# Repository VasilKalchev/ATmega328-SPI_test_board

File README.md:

# ATmega328-SPI_test_board
ATmega328 test board connected to an SPI device and a few inputs and outputs.

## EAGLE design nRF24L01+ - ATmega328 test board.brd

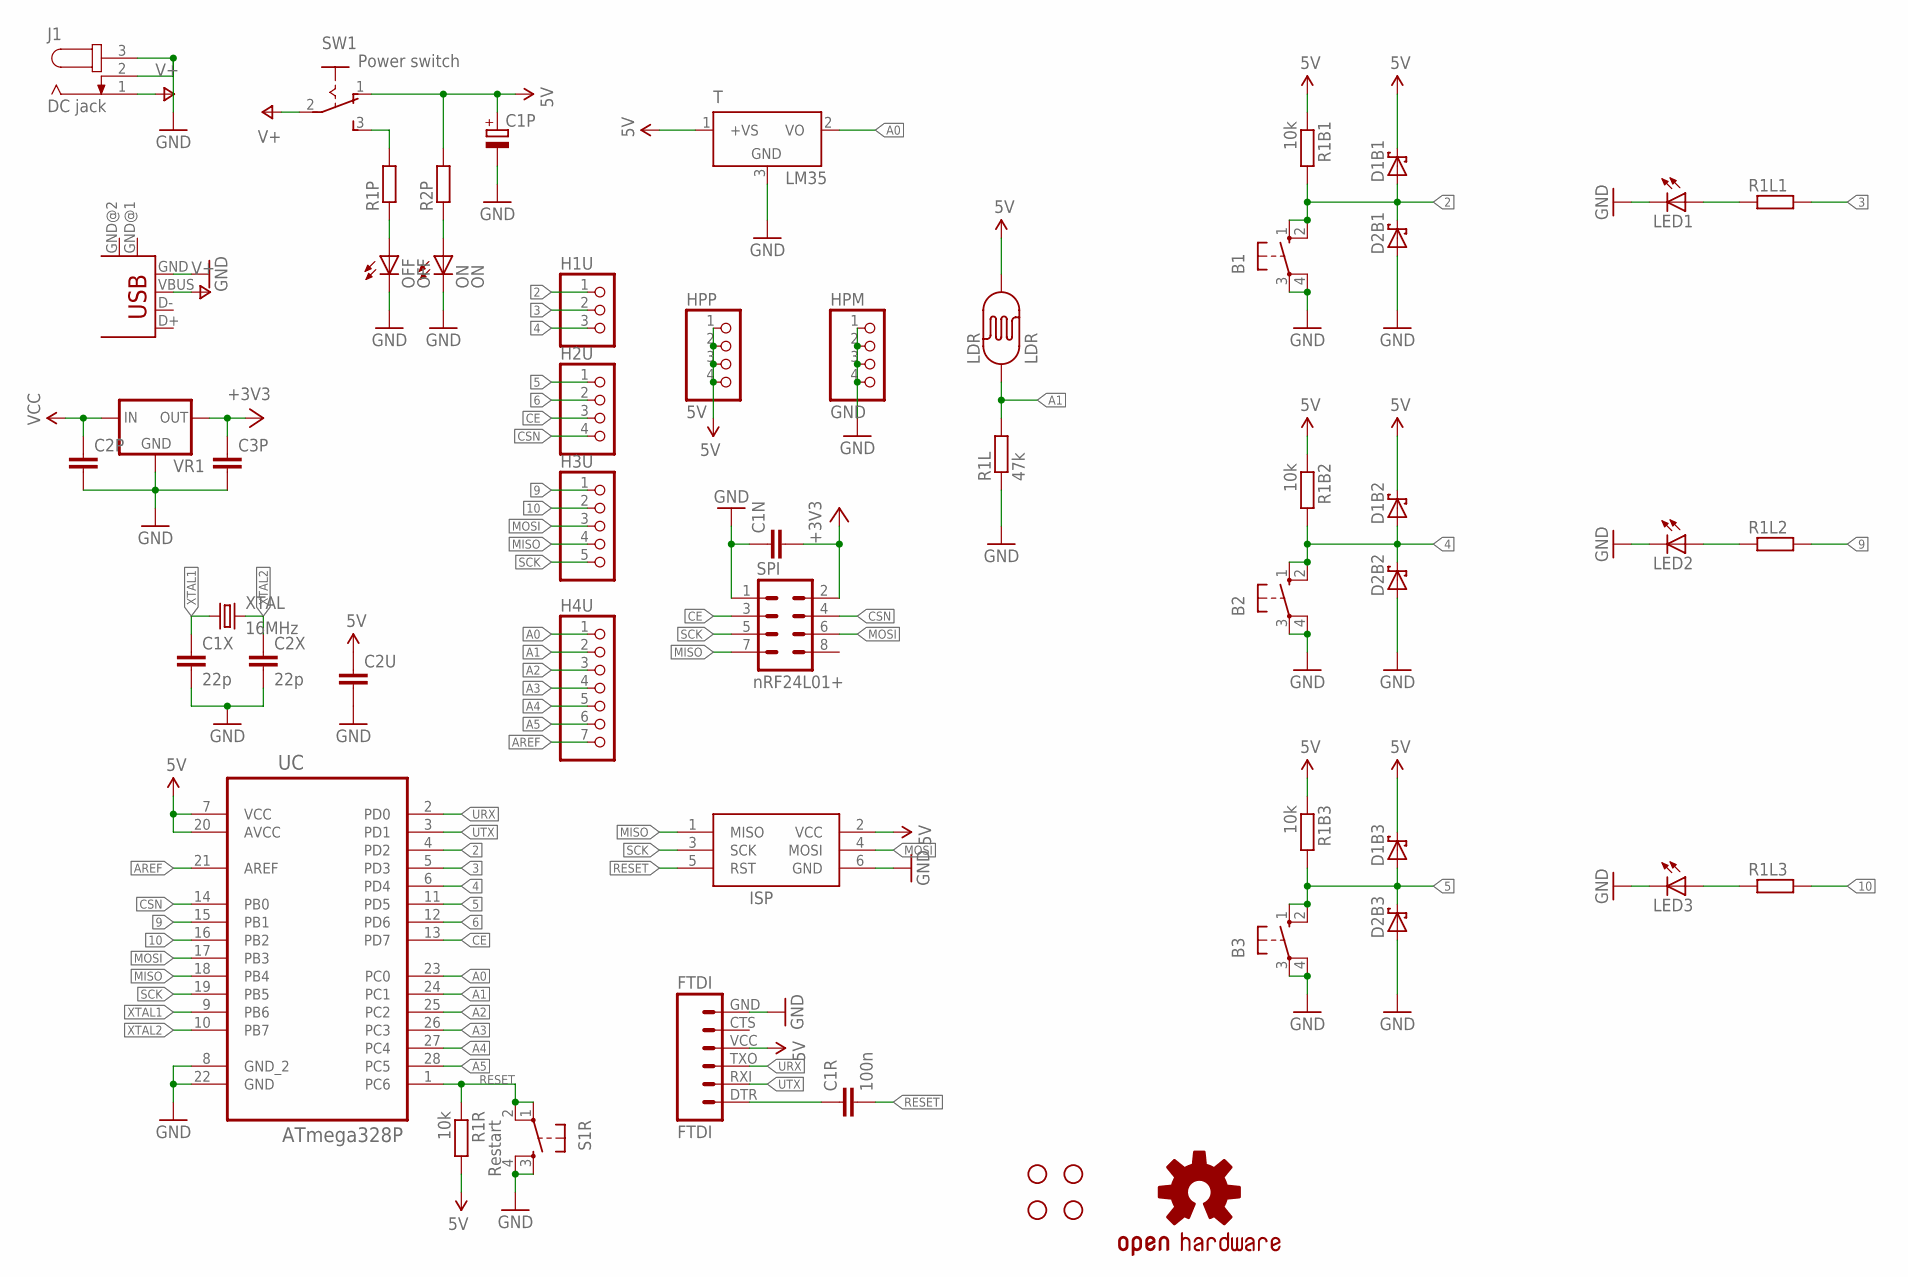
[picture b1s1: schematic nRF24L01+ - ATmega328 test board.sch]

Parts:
B1, B2, B3: 40-XX; B3F-40XX
C1N, C2P, C3P: C-EU050-025X075; C050-025X075
C1P: CPOL-EUE5-8.5; E5-8,5
C1R: 100n; C050-025X075
C1X, C2X: 22p; C025-025X050
C2U: C-EU050-055X075; C050-055X075
D1B1, D1B2, D1B3, D2B1, D2B2, D2B3: SCHOTTKY-DIODEDO41-7; DO41-7
FTDI: FTDI; FTDI_BASIC
H1, H2, H3, H4: STAND-OFF
H1U: PINHD-1X3; 1X03
H2U: PINHD-1X4; 1X04
H3U: PINHD-1X5; 1X05
H4U: PINHD-1X7; 1X07
HPM: GND; 1X04
HPP: 5V; 1X04
ISP: AVRISP-6; AVRISP
J1: DC jack; SPC4078
J2: USB mini; USB-MB-H
LDR: LDR; PHOTOCELL
LED1, LED2, LED3: LED5MM
LOGO1: OSHW-LOGOM-COPPER; OSHW-LOGO-M_COPPER
OFF: OFF; LED3MM
ON: ON; LED3MM
R1B1, R1B2, R1B3, R1R: 10k; 0207/7
R1L: 47k; 0207/7
R1L1, R1L2, R1L3, R1P, R2P: R-EU_0207/7; 0207/7
S1R: Restart; TACTILE-PTH
SPI: nRF24L01+; 2X4; MPN MOD-NRF24LR
SW1: Power switch; SWITCH_2MM
T: LM35; TO92
UC: ATmega328P; DIP254P762X457-28
VR1: 78LXX
XTAL: 16MHz; HC49/S

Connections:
2: B1.1 (S), B1.2 (S1), D1B1.A, D2B1.C, H1U.1, R1B1.2, UC.4 (PD2)
3: H1U.2, R1L1.2, UC.5 (PD3)
4: B2.1 (S), B2.2 (S1), D1B2.A, D2B2.C, H1U.3, R1B2.2, UC.6 (PD4)
5: B3.1 (S), B3.2 (S1), D1B3.A, D2B3.C, H2U.1, R1B3.2, UC.11 (PD5)
5V: C1P.+, C2U.1, D1B1.C, D1B2.C, D1B3.C, FTDI.VCC (4), HPP.1, HPP.2, HPP.3, HPP.4, ISP.2 (VCC), LDR.2, R1B1.1, R1B2.1, R1B3.1, R1R.2, R2P.2, SW1.1, T.1 (+VS), UC.7 (VCC), UC.20 (AVCC)
6: H2U.2, UC.12 (PD6)
9: H3U.1, R1L2.2, UC.15 (PB1)
10: H3U.2, R1L3.2, UC.16 (PB2)
+3V3: C1N.2, C3P.1, SPI.2, VR1.OUT
A0: H4U.1, T.2 (VO), UC.23 (PC0)
A1: H4U.2, LDR.1, R1L.2, UC.24 (PC1)
A2: H4U.3, UC.25 (PC2)
A3: H4U.4, UC.26 (PC3)
A4: H4U.5, UC.27 (PC4)
A5: H4U.6, UC.28 (PC5)
AREF: H4U.7, UC.21 (AREF)
CE: H2U.3, SPI.3, UC.13 (PD7)
CSN: H2U.4, SPI.4, UC.14 (PB0)
GND: B1.3, B1.4 (P1), B2.3, B2.4 (P1), B3.3, B3.4 (P1), C1N.1, C1P.-, C1X.2, C2P.2, C2U.2, C2X.2, C3P.2, D2B1.A, D2B2.A, D2B3.A, FTDI.GND (6), HPM.1, HPM.2, HPM.3, HPM.4, ISP.6 (GND), J1.2, J1.3, J2.GND, LED1.K (C), LED2.K (C), LED3.K (C), OFF.K (C), ON.K (C), R1L.1, S1R.3, S1R.4, SPI.1, T.3 (GND), UC.8 (GND_2), UC.22 (GND), VR1.GND
MISO: H3U.4, ISP.1 (MISO), SPI.7, UC.18 (PB4)
MOSI: H3U.3, ISP.4 (MOSI), SPI.6, UC.17 (PB3)
unnamed: LED1.A, R1L1.1
unnamed: ON.A, R2P.1
unnamed: C1R.1, FTDI.DTR (1)
unnamed: OFF.A, R1P.1
unnamed: R1P.2, SW1.3
unnamed: LED2.A, R1L2.1
unnamed: LED3.A, R1L3.1
RESET: C1R.2, ISP.5 (RST), R1R.1, S1R.1, S1R.2, UC.1 (PC6)
SCK: H3U.5, ISP.3 (SCK), SPI.5, UC.19 (PB5)
URX: FTDI.TXO (3), UC.2 (PD0)
UTX: FTDI.RXI (2), UC.3 (PD1)
V+: J1.1, J2.VBUS, SW1.2
VCC: C2P.1, VR1.IN
XTAL1: C1X.1, UC.9 (PB6), XTAL.1
XTAL2: C2X.1, UC.10 (PB7), XTAL.2

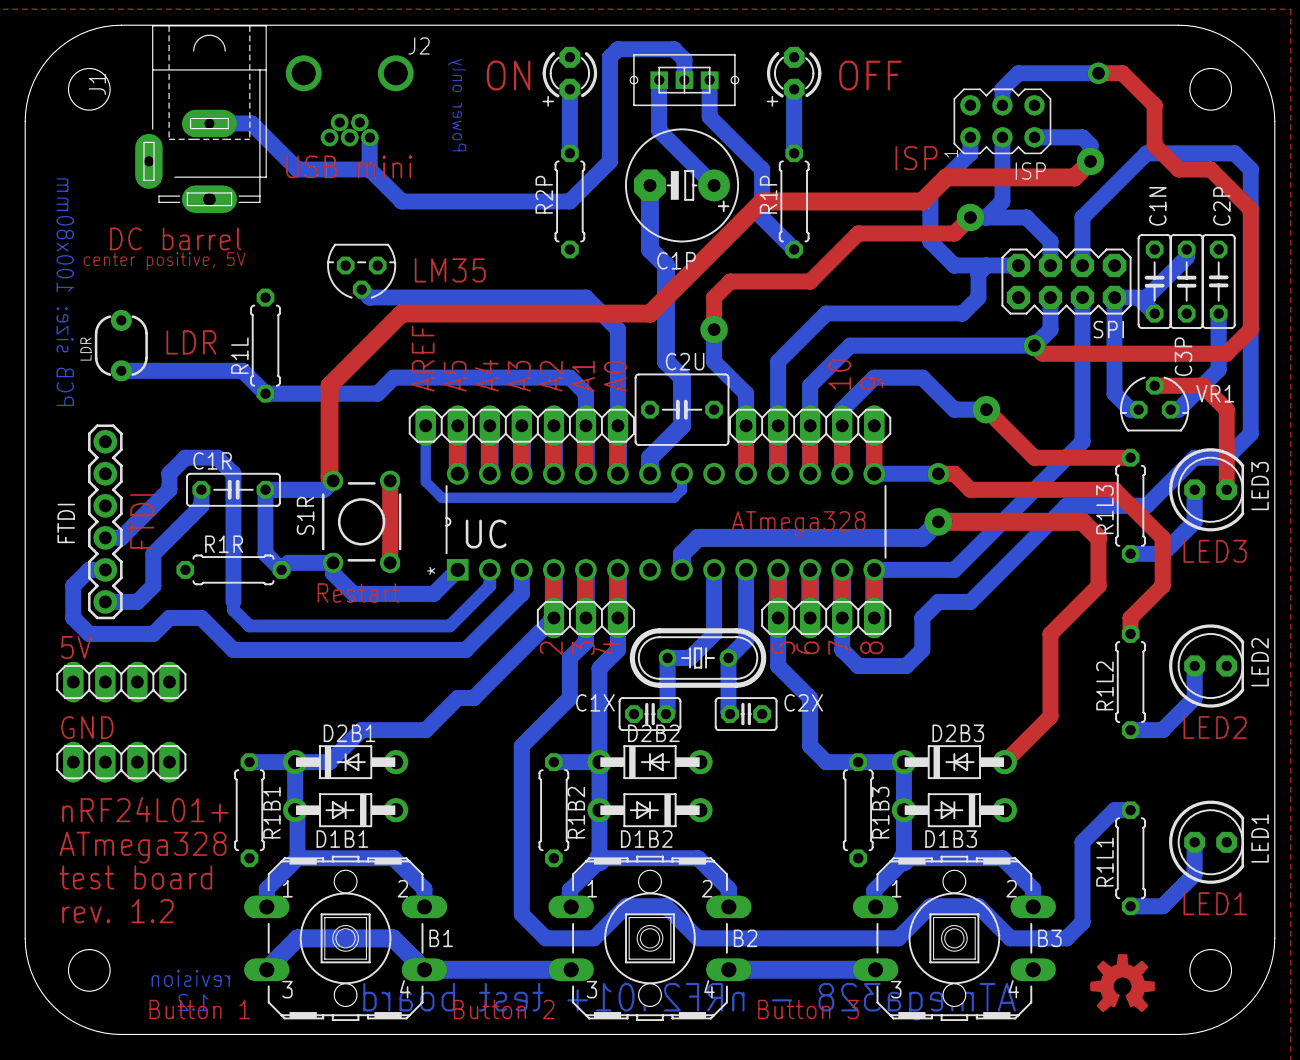
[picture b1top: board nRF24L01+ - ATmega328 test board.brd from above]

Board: 2 copper layers, 99.1 x 80.0 mm, 55 parts (0 on the bottom side), 36 nets.

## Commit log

2017-05-01 :tada: Added .gitattributes & .gitignore files
2017-05-01 Added 3.3V regulator
2017-05-01 Exported images
2017-05-01 3d model
2017-05-04 Corrections

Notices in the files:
parts and their libraries:
SparkFun-Connectors: Licensing: Creative Commons ShareAlike 4.0 International - https://creativecommons.org/licenses/by-sa/4.0
